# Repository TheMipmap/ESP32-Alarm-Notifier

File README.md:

# ESP32-Alarm-Notifier
An ESP32-based system for monitoring 24V analog alarm signals triggered by sensors throughout a farm. The software side of the system is made with ESPHome, Node-RED and Home Assistant. The ESP32 used is the Olimex ESP32-POE-ISO-IND, but any PoE powered ESP32 would have worked.

<Picture of the final setup>

## Problem description
There are 5 LEDs that represent alarms in different buildings. In order to find out whether a problem has occurred, and where said problem is, one must check these LEDs. The goal is to get these LEDs into Home Assistant as binary sensors, and notify me when a problem has occurred in any of the buildings. 

The five alarms can be simplified as seperate 24V circuits each containing an LED and an on/off switch.

<Picture of a simplified circuit>

## Hardware & Solution
As I wanted to learn the basics of designing PCBs, I figured i could try to design a simple PCB that could solve this problem. Additionally, the ESP32 had to be powered using PoE (to minimize cabling). After searching for boards around the internet, I settled for the Olimex ESP32-POE board. The idea was simple. I wanted to intercept the signal on each LED using optocouplers. The collectors were connected to their own GPIO pin, with ESP32's internal pullup resistors, and the emitters were connected to ground. The simplified circuit with an optocoupler can be seen in the picture below.

<Picture of simplified circuit with opto>

The KiCAD files for the final design of the PCB can be found in the repository. 

<Picture of the PCB schematics>

<Picture of the PCB circuit>

<Render of the PCB in KiCAD>

<Picture of the PCB with components>

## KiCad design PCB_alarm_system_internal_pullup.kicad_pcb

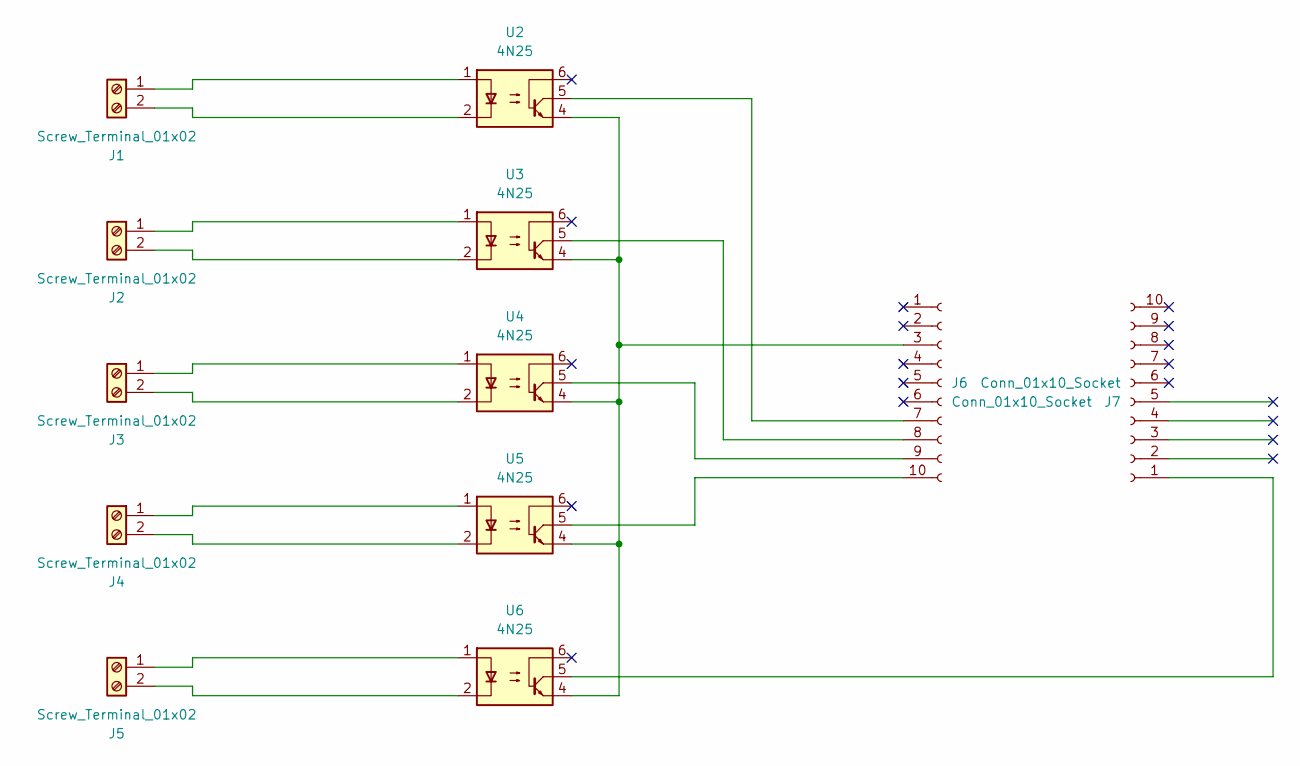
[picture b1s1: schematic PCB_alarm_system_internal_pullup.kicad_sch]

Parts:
J1, J2, J3, J4, J5: Screw_Terminal_01x02; TerminalBlock_Phoenix_MKDS-1,5-2-5.08_1x02_P5.08mm_Horizont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
J6, J7: Conn_01x10_Socket; PinSocket_1x10_P2.54mm_Vertical
U2, U3, U4, U5, U6: 4N25; DIP-6_W7.62mm

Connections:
unnamed: J1.1, U2.1
unnamed: J1.2, U2.2
unnamed: J2.1, U3.1
unnamed: J2.2, U3.2
unnamed: J3.1, U4.1
unnamed: J3.2, U4.2
unnamed: J4.1, U5.1
unnamed: J4.2, U5.2
unnamed: J5.1, U6.1
unnamed: J5.2, U6.2
unnamed: J6.3, U2.4, U3.4, U4.4, U5.4, U6.4
unnamed: J6.7, U2.5
unnamed: J6.8, U3.5
unnamed: J6.9, U4.5
unnamed: J6.10, U5.5
unnamed: J7.1, U6.5

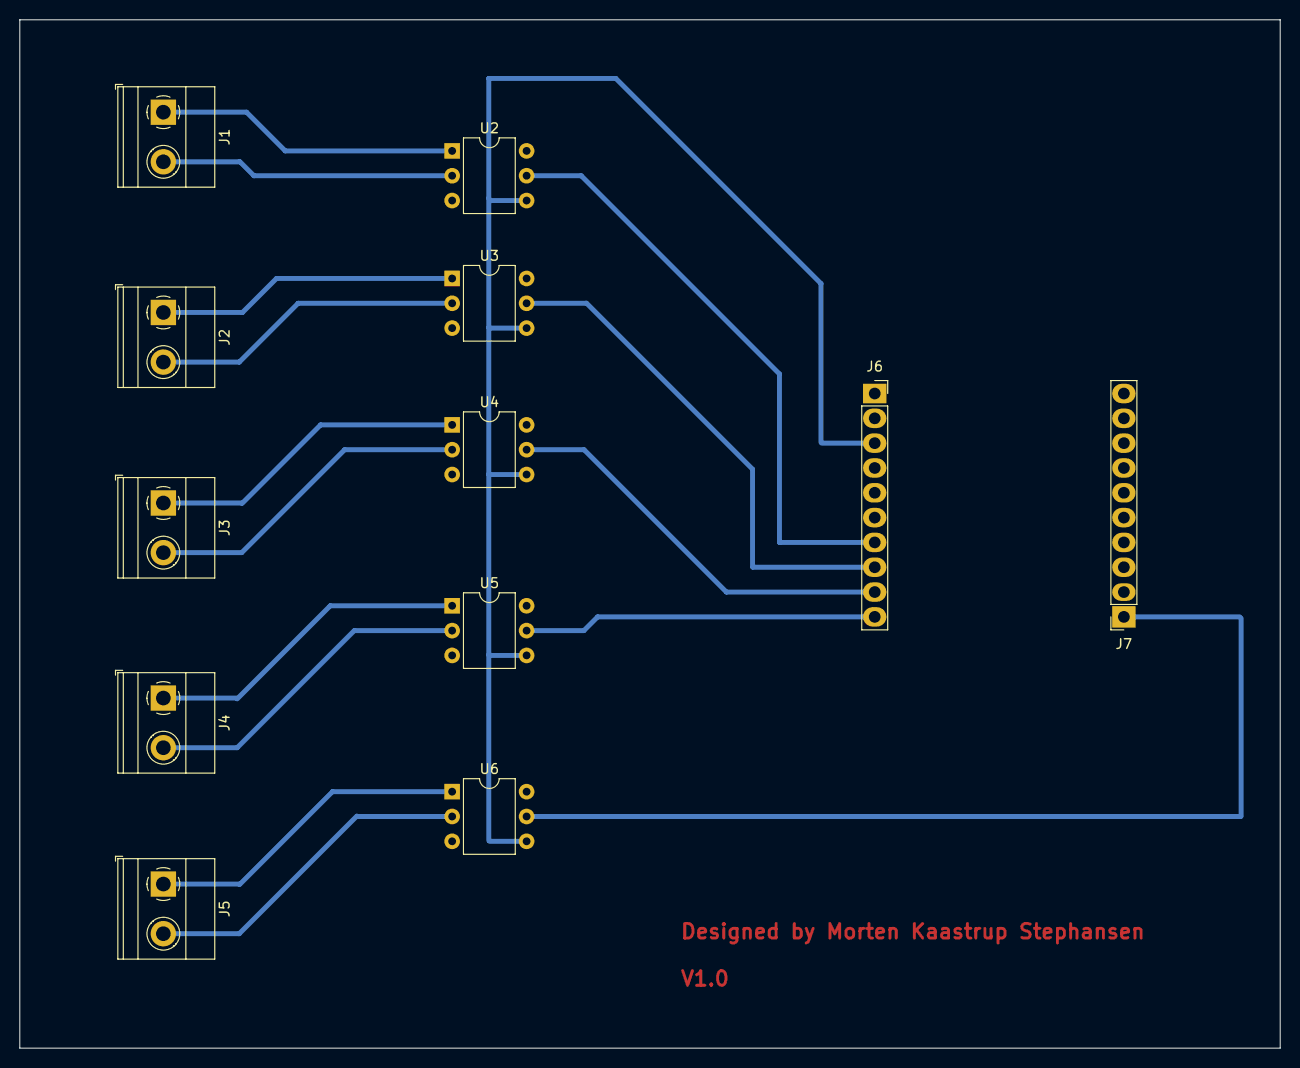
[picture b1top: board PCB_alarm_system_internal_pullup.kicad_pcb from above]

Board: 2 copper layers, 129.0 x 105.2 mm, 12 parts (0 on the bottom side), 16 nets.

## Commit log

2024-08-12 Added resources and KiCAD files
2024-08-12 Update README.md
    Added some pictures
2024-08-13 Added image of the setup
2024-08-13 Added picture of the PCB with component
2024-09-04 ADD: ESPHome config used in the project
